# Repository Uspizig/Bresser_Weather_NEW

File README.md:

# Bresser_Weather_NEW
Arduino/ESP32 Sketch for a CC101 Receiver 868.3MHz to Decode Weather Data of a Bresser 5in1 Weather Station(2022)

This Demo outputs the captured Weather station Values of a Bresser 5in1 Station that I found cheap on ebay

Currently supported values:
- Temp
- Humidity
- Rain
- Winddirection
- Windspeed

Link to Weatherstation-Product: (might be compatible to 6in1 as well)
https://www.ebay.de/itm/294905798218

Link to 868 MHz reciever:
https://www.ebay.de/itm/283548978565

Link to a good ESP32 Board with eink Display
https://www.ebay.de/itm/165350071073

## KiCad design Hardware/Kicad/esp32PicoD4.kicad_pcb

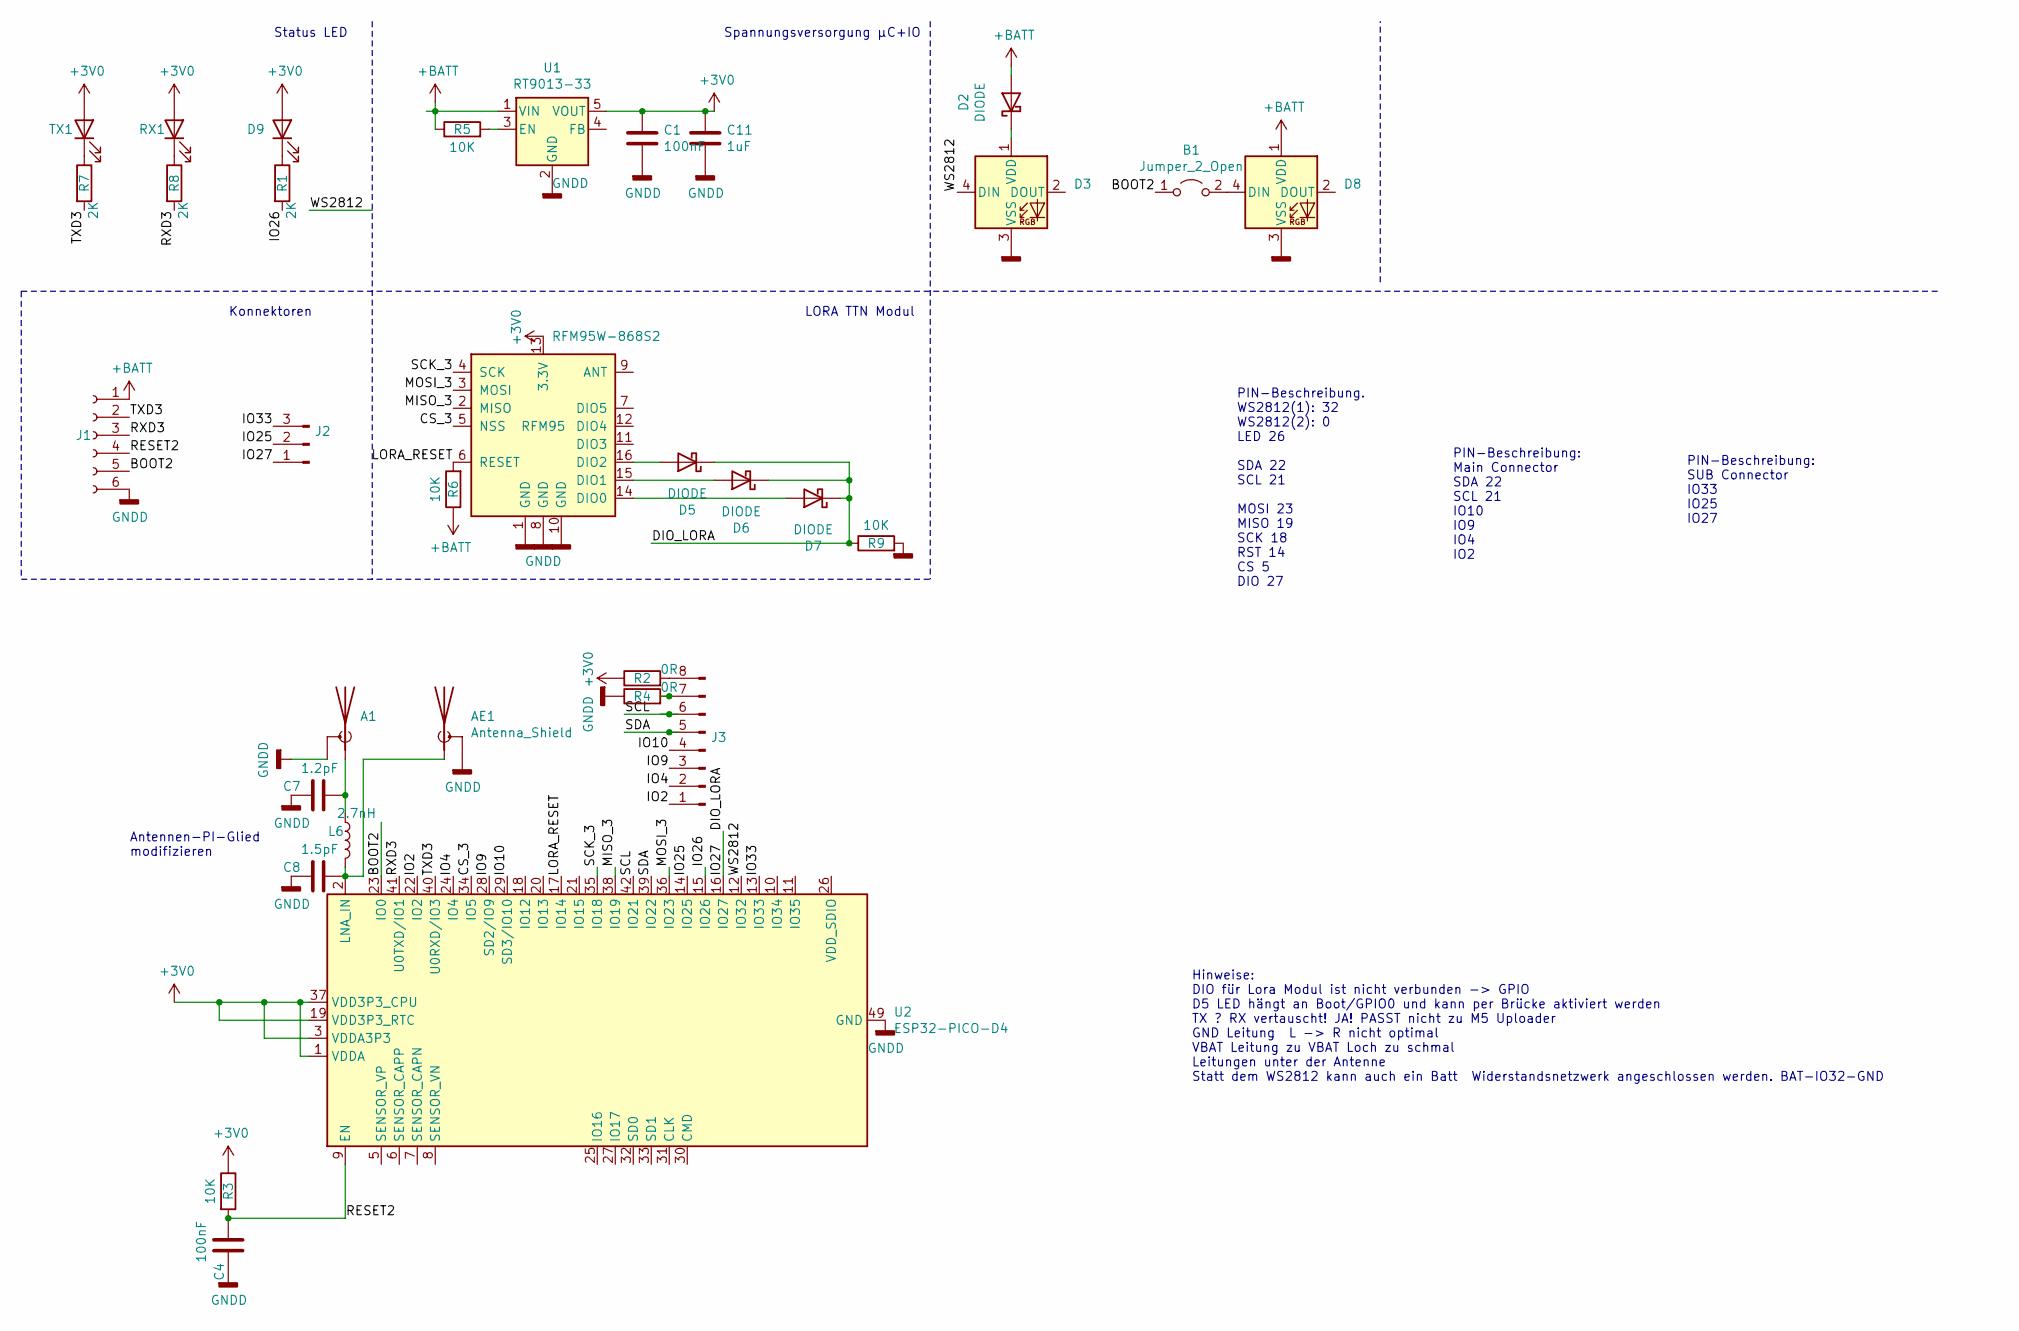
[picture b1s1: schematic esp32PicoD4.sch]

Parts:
A1: Antenna_Shield; Texas_SWRA117D_2.4GHz_Left
AE1: Antenna_Shield; U.FL_Hirose_U.FL-R-SMT-1_Vertical
B1: Jumper_2_Open; SolderJumper-2_P1.3mm_Open_RoundedPad1.0x1.5mm
C1: 100nF; C_0805_2012Metric_Pad1.18x1.45mm_HandSolder; LCSC C49678
C4: 100nF; C_0805_2012Metric_Pad1.18x1.45mm_HandSolder; LCSC C1525
C7: 1.2pF; C_0603_1608Metric_Pad1.08x0.95mm_HandSolder; LCSC C1639
C8: 1.5pF; C_0603_1608Metric_Pad1.08x0.95mm_HandSolder; LCSC C1639
C11: 1uF; C_0805_2012Metric_Pad1.18x1.45mm_HandSolder; LCSC C15849
D2, D5, D6, D7: DIODE; D_SOD-123
D3, D8: WS2812B; LED_WS2812B_PLCC4_5.0x5.0mm_P3.2mm
D32: LED; LED_0603_1608Metric_Pad1.05x0.95mm_HandSolder; LCSC C2290
J1: Conn_01x06_Female; PinHeader_1x06_P2.54mm_Vertical
J2: Conn_01x03_male; PinSocket_1x03_P2.54mm_Vertical_SMD_Pin1Right
J3: Conn_01x08_Female; PinSocket_1x08_P2.54mm_Vertical_SMD_Pin1Right
L6: 2.7nH; L_0603_1608Metric_Pad1.05x0.95mm_HandSolder; LCSC C83929
R1: 2K; R_0603_1608Metric_Pad1.05x0.95mm_HandSolder; LCSC C4109
R2, R4: 0R; R_0805_2012Metric_Pad1.20x1.40mm_HandSolder; LCSC C21189
R3: 10K; R_0603_1608Metric_Pad1.05x0.95mm_HandSolder; LCSC C25744
R5: 10K; R_0805_2012Metric_Pad1.20x1.40mm_HandSolder; LCSC C25744
R6: 10K; R_0805_2012Metric_Pad1.20x1.40mm_HandSolder; LCSC C25804
R7, R8: 2K; R_0805_2012Metric_Pad1.20x1.40mm_HandSolder; LCSC C4109
R9: 10K; R_0603_1608Metric; LCSC C25804
RFM95: RFM95W-868S2; HOPERF_RFM9XW_SMD
RX1: LED; LED_0603_1608Metric_Pad1.05x0.95mm_HandSolder; LCSC C2290
TX1: LED; LED_0603_1608Metric_Pad1.05x0.95mm_HandSolder; LCSC C2290
U1: RT9013-33; SOT-23-5_HandSoldering; LCSC C47773
U2: ESP32-PICO-D4; QFN-48-1EP_7x7mm_P0.5mm_EP5.3x5.3mm; LCSC C193707

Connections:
+3V0: C1.1, C11.1, R2.1, R3.1, RFM95.13 (3.3V), RX1.2 (A), TX1.2 (A), U1.5 (VOUT), U2.1 (VDDA), U2.3 (VDDA3P3), U2.4 (VDDA3P3), U2.19 (VDD3P3_RTC), U2.37 (VDD3P3_CPU), U2.43 (VDDA), U2.46 (VDDA); also elsewhere on the board
+BATT: D2.2 (A), D8.1 (VDD), J1.1, R5.1, R6.1, U1.1 (VIN)
/BOOT2: B1.1 (A), J1.5, U2.23 (IO0)
/CS_3: RFM95.5 (NSS), U2.34 (IO5)
/DIO_LORA: D5.1 (K), D6.1 (K), D7.1 (K), J2.1, R9.1, U2.16 (IO27)
/IO2: J3.1, U2.22 (IO2)
/IO4: J3.2, U2.24 (IO4)
/IO9: J3.3, U2.28 (SD2/IO9)
/IO10: J3.4, U2.29 (SD3/IO10)
/IO25: J2.2, U2.14 (IO25)
/IO26: R1.2, U2.15 (IO26)
/IO33: J2.3, U2.13 (IO33)
/LORA_RESET: R6.2, RFM95.6 (RESET), U2.17 (IO14)
/MISO_3: RFM95.2 (MISO), U2.38 (IO19)
/MOSI_3: RFM95.3 (MOSI), U2.36 (IO23)
/RESET2: C4.1, J1.4, R3.2, U2.9 (EN)
/RXD3: J1.3, R8.2, U2.41 (U0TXD/IO1)
/SCK_3: RFM95.4 (SCK), U2.35 (IO18)
/SCL: J3.6, U2.42 (IO21)
/SDA: J3.5, U2.39 (IO22)
/TXD3: J1.2, R7.2, U2.40 (U0RXD/IO3)
/WS2812: D3.4 (DIN), U2.12 (IO32)
GNDD: A1.2 (Shield), AE1.2 (Shield), C1.2, C4.2, C7.2, C8.2, C11.2, D3.3 (VSS), D8.3 (VSS), J1.6, R4.1, R9.2, RFM95.1 (GND), RFM95.8 (GND), RFM95.10 (GND), U1.2 (GND), U2.49 (GND)
unnamed: A1.1 (A), C7.1, L6.1
unnamed: AE1.1 (A), C8.1, L6.2, U2.2 (LNA_IN)
unnamed: B1.2 (B), D8.4 (DIN)
unnamed: D2.1 (K), D3.1 (VDD)
unnamed: D5.2 (A), RFM95.16 (DIO2)
unnamed: D6.2 (A), RFM95.15 (DIO1)
unnamed: D7.2 (A), RFM95.14 (DIO0)
unnamed 30: R1.1; also elsewhere on the board
unnamed: J3.7, R4.2
unnamed: J3.8, R2.2
unnamed: R5.2, U1.3 (EN)
unnamed: R7.1, TX1.1 (K)
unnamed: R8.1, RX1.1 (K)

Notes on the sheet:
Spannungsversorgung µC+IO
LORA TTN Modul
Antennen-PI-Glied modifizieren
Hinweise: DIO für Lora Modul ist nicht verbunden -> GPIO D5 LED hängt an Boot/GPIO0 und kann per Brücke aktiviert werden TX ? RX vertauscht! JA! PASST nicht zu M5 Uploader GND Leitung L -> R nicht optimal VBAT Leitung zu VBAT Loch zu schmal Leitungen unter der Antenne Statt dem WS2812 kann auch ein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
PIN-Beschreibung. WS2812(1): 32 WS2812(2): 0 LED 26 SDA 22 SCL 21 MOSI 23 MISO 19 SCK 18 RST 14 CS 5 DIO 27
PIN-Beschreibung: Main Connector SDA 22 SCL 21 IO10 IO9 IO4 IO2
PIN-Beschreibung: SUB Connector IO33 IO25 IO27
Konnektoren
Status LED

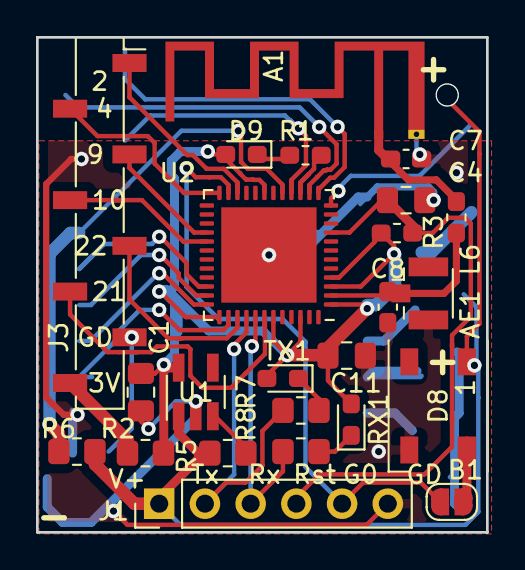
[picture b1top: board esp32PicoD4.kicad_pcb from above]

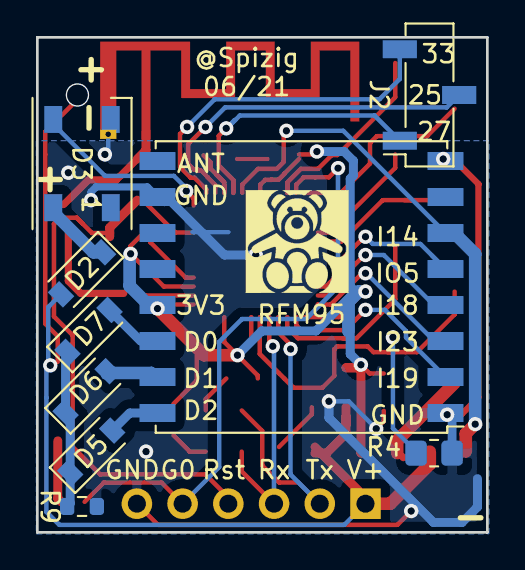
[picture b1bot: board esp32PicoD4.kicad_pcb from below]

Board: 2 copper layers, 25.0 x 27.5 mm, 33 parts (9 on the bottom side), 36 nets.

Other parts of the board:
D9: LED; LED_0603_1608Metric_Pad1.05x0.95mm_HandSolder

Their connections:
+3V0: D9.2; also elsewhere on the board
unnamed 30: D9.1; also elsewhere on the board
